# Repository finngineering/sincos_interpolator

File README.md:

# SinCos Interpolator
The SinCos Interpolator reads the analog signals from (e.g. Heidenhain) linear scales and converts them into digital quadrature signals. The design is based on the iC-NV chip by iC-Haus. This board performs essentially the same function as Heidenhain "EXE" converters. The design was created for Heidenhain LS 403 linear scales with 11 uA peak-to-peak signals. Through different component values and solder jumper configuration, it should be usable also for other linear scales and similar transducers.

## Disclaimer
As of 2025-01-18, the latest version is 1.4 (which has RJ45 jacks rotated 180° and improved crowbar circuit, compared to version 1.3). This design has been tested to a small extent and is working. However, there appears to be reason to make some accomodations for low pass filtering of the input signals. Version 1.0 tested appeared to be otherwise working, but had power/ground swapped for the MC3487DX IC. A RJ45 jack for the encoder side has also been added since version 1.0.

## Features
- Converts analog sine/cosine signals into digital quadrature outputs
- Interpolation factor selectable by solder jumpers
- Suitable for different type of input signals by resistor selection and solder jumper configuration
- Single ended or differential outputs (the latter with additional MC3487DX IC)
- Support for index/reference signal
- Normal screw terminal blocks with 5.08 mm raster for connections
- Optionally shielded RJ45 connectors for inputs and/or outputs
- Reverse polarity protection
- Overvoltage protection through crowbar circuit
- Using mainly through hole component for ease of soldering
- Two layer board with components on top side only

## Using with 11 uA peak-to-peak transducers (e.g. LS 403)

By component values and solder jumper configuration, the board can be adapted to different type of transducers. For 11 uA peak-to-peak transducers, resistors R11, R12, R21 and R22 should have a 25 kOhm resistance and VREF jumpers JP11 and JP21 should be shorted by soldering. Jumper JP2/SG1 should be soldered "LO" (circuit ground) and JP1/SG0 should be left open to allow signal amplitues of up to 1 Vpp. Jumper JP5/ROT can be soldered "LO" unless some specific phase behaviour is required. Jumpers JP4/SF1 and JP3/SF0 are both left open for an interpolation factor of 5. With the 20 um periodicity of the LS 402 linear scales, this gives an output resolution of 1 um (provided the flanks of the A/B signals are "counted"). Jumper JP6/RCLK should be soldered short unless minimun transition distance needs to be adjusted. For all suggestions given in this paragraph, the iC-NV datasheet is not exceptionally clear, and you may want to do you own interpretation.

Single ended or differential outputs are selected by jumpers JP12-JP13, JP22-JP23 and JP32-JP33. In the open state, differential outputs are used, which also requires the board to be populated with the MC3487DX IC. In case single ended signals are preferred, the MC3487DX is left out and the aforementioned jumpers are soldered short. This connects the output from the iC-NV directly to the "positive" output signal terminals and the "negative" signal terminals are tied to ground.

One of the ground terminals was separated out as shield in version 1.3. This can be connected through (wihtout connecting it to ground) by soldering short JP8. Both input/output ends can also be tied to ground individually through JP7/JP9.

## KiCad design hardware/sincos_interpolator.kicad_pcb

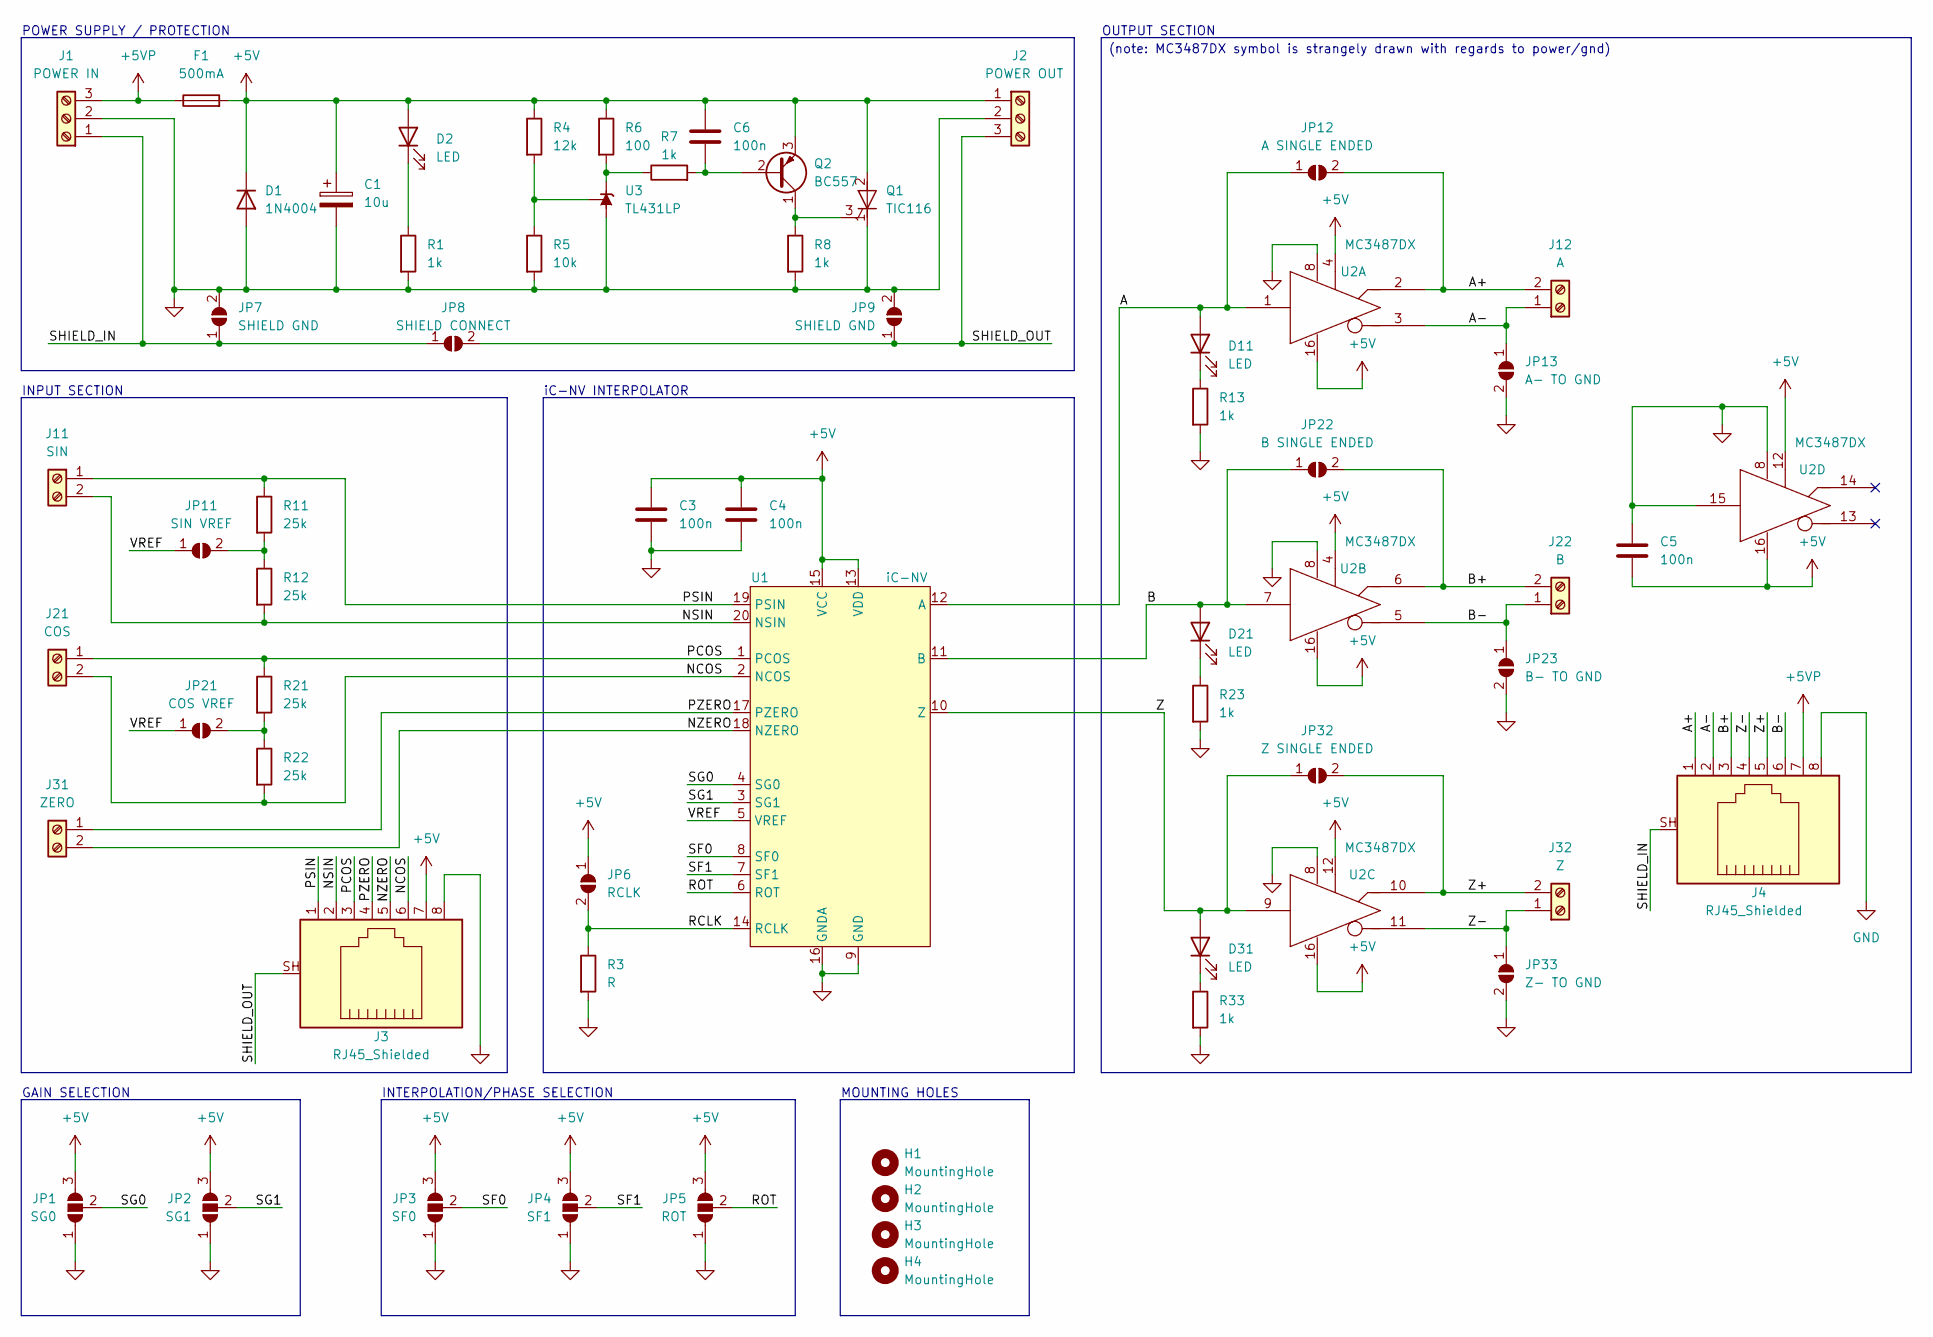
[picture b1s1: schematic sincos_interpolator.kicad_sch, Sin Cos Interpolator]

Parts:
C1: 10u; CP_Radial_D7.5mm_P2.50mm
C3, C4, C5, C6: 100n; C_Disc_D5.0mm_W2.5mm_P2.50mm
D1: 1N4004; D_DO-41_SOD81_P10.16mm_Horizontal
D2, D11, D21, D31: LED; LED_D3.0mm
F1: 500mA; Fuseholder_Clip-5x20mm_Littelfuse_520_Inline_P20.50x5.80mm_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
H1, H2, H3, H4: MountingHole; MountingHole_3.2mm_M3_ISO14580
J1: POWER IN; TerminalBlock_Phoenix_MKDS-1,5-3-5.08_1x03_P5.08mm_Horizont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
J2: POWER OUT; TerminalBlock_Phoenix_MKDS-1,5-3-5.08_1x03_P5.08mm_Horizont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
J3, J4: RJ45_Shielded; RJ45_Molex_855085001
J11: SIN; TerminalBlock_Phoenix_MKDS-1,5-2-5.08_1x02_P5.08mm_Horizont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
J12: A; TerminalBlock_Phoenix_MKDS-1,5-2-5.08_1x02_P5.08mm_Horizont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
J21: COS; TerminalBlock_Phoenix_MKDS-1,5-2-5.08_1x02_P5.08mm_Horizont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
J22: B; TerminalBlock_Phoenix_MKDS-1,5-2-5.08_1x02_P5.08mm_Horizont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
J31: ZERO; TerminalBlock_Phoenix_MKDS-1,5-2-5.08_1x02_P5.08mm_Horizont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
J32: Z; TerminalBlock_Phoenix_MKDS-1,5-2-5.08_1x02_P5.08mm_Horizont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
JP1: SG0; SolderJumper-3_P1.3mm_Open_RoundedPad1.0x1.5mm
JP2: SG1; SolderJumper-3_P1.3mm_Open_RoundedPad1.0x1.5mm
JP3: SF0; SolderJumper-3_P1.3mm_Open_RoundedPad1.0x1.5mm
JP4: SF1; SolderJumper-3_P1.3mm_Open_RoundedPad1.0x1.5mm
JP5: ROT; SolderJumper-3_P1.3mm_Open_RoundedPad1.0x1.5mm
JP6: RCLK; SolderJumper-2_P1.3mm_Open_RoundedPad1.0x1.5mm
JP7, JP9: SHIELD GND; SolderJumper-2_P1.3mm_Open_RoundedPad1.0x1.5mm
JP8: SHIELD CONNECT; SolderJumper-2_P1.3mm_Open_RoundedPad1.0x1.5mm
JP11: SIN VREF; SolderJumper-2_P1.3mm_Open_RoundedPad1.0x1.5mm
JP12: A SINGLE ENDED; SolderJumper-2_P1.3mm_Open_RoundedPad1.0x1.5mm
JP13: A- TO GND; SolderJumper-2_P1.3mm_Open_RoundedPad1.0x1.5mm
JP21: COS VREF; SolderJumper-2_P1.3mm_Open_RoundedPad1.0x1.5mm
JP22: B SINGLE ENDED; SolderJumper-2_P1.3mm_Open_RoundedPad1.0x1.5mm
JP23: B- TO GND; SolderJumper-2_P1.3mm_Open_RoundedPad1.0x1.5mm
JP32: Z SINGLE ENDED; SolderJumper-2_P1.3mm_Open_RoundedPad1.0x1.5mm
JP33: Z- TO GND; SolderJumper-2_P1.3mm_Open_RoundedPad1.0x1.5mm
Q1: TIC116; TO-220-3_Vertical
Q2: BC557; TO-92_Inline
R1, R7, R8, R13, R23, R33: 1k; R_Axial_DIN0207_L6.3mm_D2.5mm_P10.16mm_Horizontal
R3: R; R_Axial_DIN0207_L6.3mm_D2.5mm_P10.16mm_Horizontal
R4: 12k; R_Axial_DIN0207_L6.3mm_D2.5mm_P10.16mm_Horizontal
R5: 10k; R_Axial_DIN0207_L6.3mm_D2.5mm_P10.16mm_Horizontal
R6: 100; R_Axial_DIN0207_L6.3mm_D2.5mm_P10.16mm_Horizontal
R11, R12, R21, R22: 25k; R_Axial_DIN0207_L6.3mm_D2.5mm_P2.54mm_Vertical
U1: iC-NV; TSSOP-20_4.4x6.5mm_P0.65mm
U2: MC3487DX; SOIC-16_3.9x9.9mm_P1.27mm
U3: TL431LP; TO-92_Inline

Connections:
+5V: C1.1, C3.1, C4.1, C5.2, C6.1, D1.1 (K), D2.2 (A), F1.2, J2.1, J3.7, JP1.3 (B), JP2.3 (B), JP3.3 (B), JP4.3 (B), JP5.3 (B), JP6.1 (A), Q1.2 (A), Q2.3 (E), R4.1, R6.1, U1.13 (VDD), U1.15 (VCC), U2.4 (ENABLE), U2.12 (ENABLE), U2.16 (VCC)
+5VP: F1.1, J1.3, J4.7
/A: D11.2 (A), JP12.1 (A), U1.12 (A), U2.1 (INPUT)
/A+: J4.1, J12.2, JP12.2 (B), U2.2 (OUT+)
/A-: J4.2, J12.1, JP13.1 (A), U2.3 (OUT-)
/B: D21.2 (A), JP22.1 (A), U1.11 (B), U2.7 (INPUT)
/B+: J4.3, J22.2, JP22.2 (B), U2.6 (OUT+)
/B-: J4.6, J22.1, JP23.1 (A), U2.5 (OUT-)
/NCOS: J3.6, J21.2, R22.2, U1.2 (NCOS)
/NSIN: J3.2, J11.2, R12.2, U1.20 (NSIN)
/NZERO: J3.5, J31.2, U1.18 (NZERO)
/PCOS: J3.3, J21.1, R21.1, U1.1 (PCOS)
/PSIN: J3.1, J11.1, R11.1, U1.19 (PSIN)
/PZERO: J3.4, J31.1, U1.17 (PZERO)
/RCLK: JP6.2 (B), R3.1, U1.14 (RCLK)
/ROT: JP5.2 (C), U1.6 (ROT)
/SF0: JP3.2 (C), U1.8 (SF0)
/SF1: JP4.2 (C), U1.7 (SF1)
/SG0: JP1.2 (C), U1.4 (SG0)
/SG1: JP2.2 (C), U1.3 (SG1)
/SHIELD_IN: J1.1, J4.SH, JP7.1 (A), JP8.1 (A)
/SHIELD_OUT: J2.3, J3.SH, JP8.2 (B), JP9.1 (A)
/VREF: JP11.1 (A), JP21.1 (A), U1.5 (VREF)
/Z: D31.2 (A), JP32.1 (A), U1.10 (Z), U2.9 (INPUT)
/Z+: J4.5, J32.2, JP32.2 (B), U2.10 (OUT+)
/Z-: J4.4, J32.1, JP33.1 (A), U2.11 (OUT-)
GND: C1.2, C3.2, C4.2, C5.1, D1.2 (A), J1.2, J2.2, J3.8, J4.8, JP1.1 (A), JP2.1 (A), JP3.1 (A), JP4.1 (A), JP5.1 (A), JP7.2 (B), JP9.2 (B), JP13.2 (B), JP23.2 (B), JP33.2 (B), Q1.1 (K), R1.2, R3.2, R5.2, R8.2, R13.2, R23.2, R33.2, U1.9 (GND), U1.16 (GNDA), U2.8 (GND), U2.15 (INPUT), U3.2 (A)
unnamed: C6.2, Q2.2 (B), R7.2
unnamed: D2.1 (K), R1.1
unnamed: D11.1 (K), R13.1
unnamed: D21.1 (K), R23.1
unnamed: D31.1 (K), R33.1
unnamed: JP11.2 (B), R11.2, R12.1
unnamed: JP21.2 (B), R21.2, R22.1
unnamed: Q1.3 (G), Q2.1 (C), R8.1
unnamed: R4.2, R5.1, U3.1 (REF)
unnamed: R6.2, R7.1, U3.3 (K)

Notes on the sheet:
POWER SUPPLY / PROTECTION
OUTPUT SECTION
INPUT SECTION
MOUNTING HOLES
iC-NV INTERPOLATOR
(note: MC3487DX symbol is strangely drawn with regards to power/gnd)
GAIN SELECTION
INTERPOLATION/PHASE SELECTION

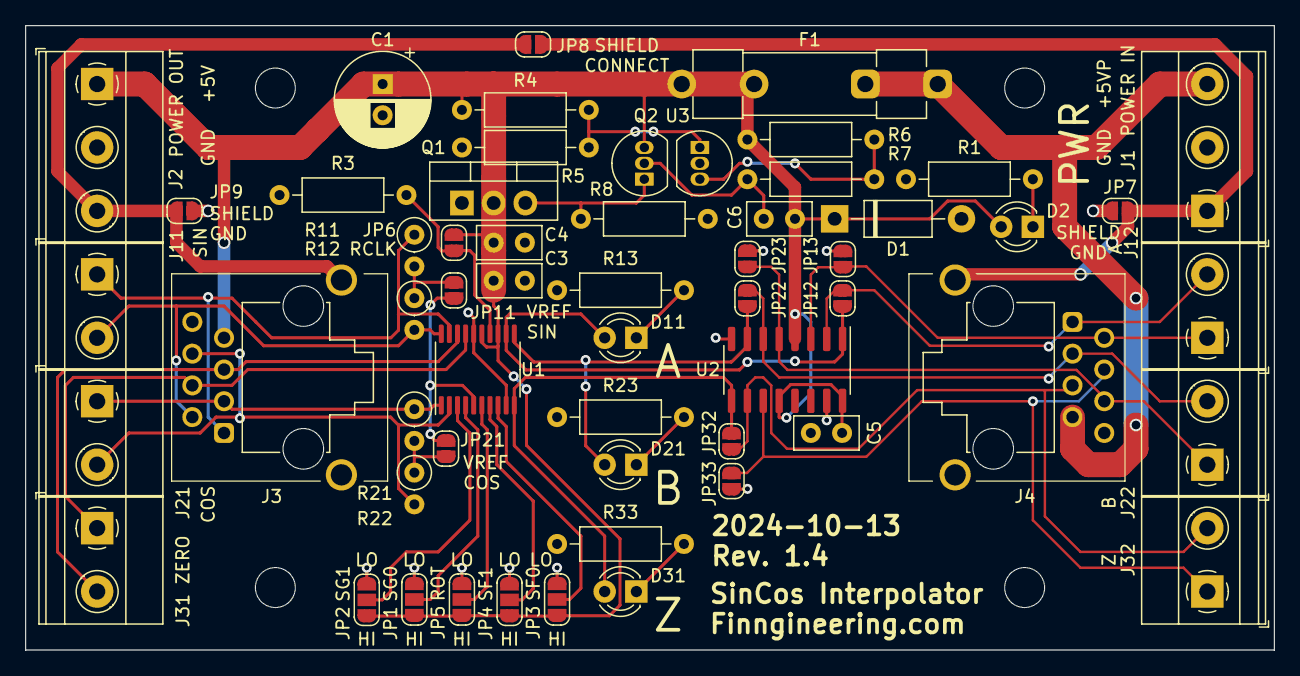
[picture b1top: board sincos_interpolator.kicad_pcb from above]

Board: 2 copper layers, 100.0 x 50.0 mm, 61 parts (0 on the bottom side), 37 nets.

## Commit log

2023-08-19 Update README.md
    Initial description
2023-08-19 Hardware version 1.1
2023-08-19 Added board render to the description
2023-08-19 Added schematic as pdf
2023-08-20 New component references and fab outputs
2023-08-22 Corrected MC3487DX power polarity and separated shield
2024-10-06 Exported schematic for version 1.3
2025-01-18 RJ45 jacks rotated 180 degrees
    RJ45 jacks rotated 180 degrees to allow the used of angled RJ45 jacks
2025-01-18 Updated board 3d view to match current design
2025-05-22 Updated pdf schematic to match version 1.4
